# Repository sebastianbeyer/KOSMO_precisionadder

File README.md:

Precision adder based on [Doepfer A185-2](https://doepfer.de/a1852.htm) in KOSMO format.

You can use precision opamps, but I found that simple TL074 also work.
I could not get the 1V reference voltage to be exactly 1V, maybe my regulator was not great or my resitors were a bit off. 
I would suggest to use not 100 ohms for that, but maybe 500?

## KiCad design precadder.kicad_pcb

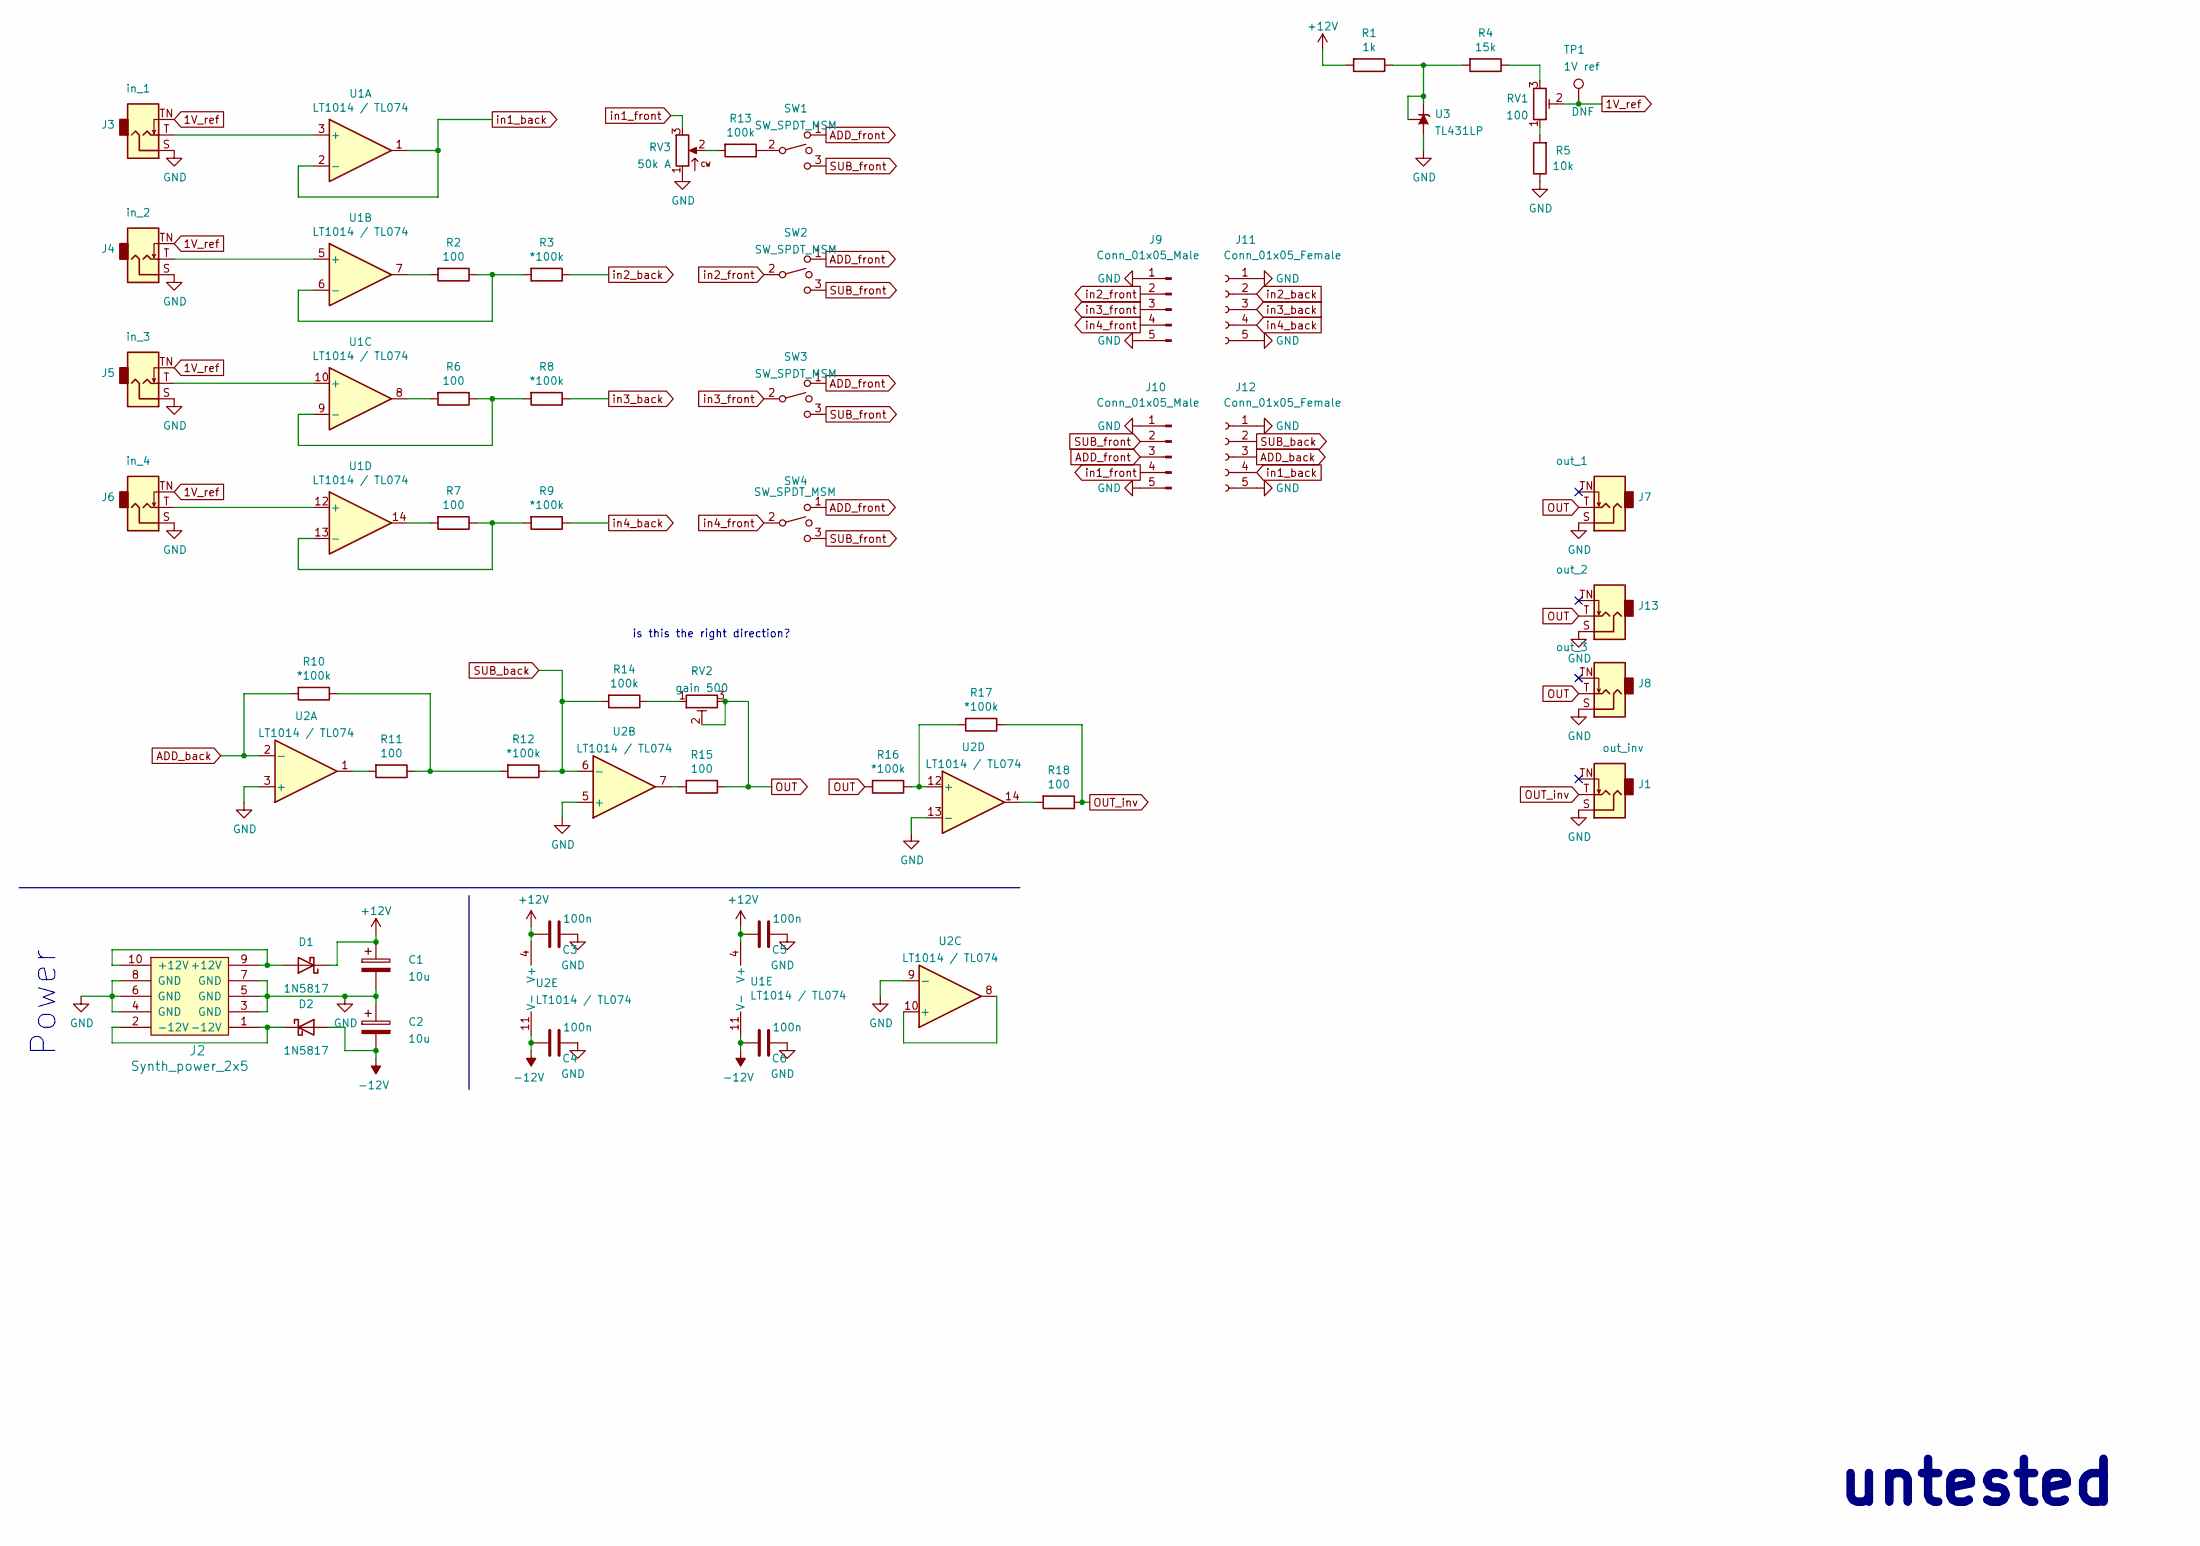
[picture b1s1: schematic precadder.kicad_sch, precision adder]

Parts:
C1, C2: 10u; CP_Radial_D6.3mm_P2.50mm
C3, C4, C5, C6: 100n; C_Disc_D3.0mm_W1.6mm_P2.50mm
D1, D2: 1N5817; D_DO-41_SOD81_P10.16mm_Horizontal
J1: out_inv; Jack_6.35mm_PJ_629HAN
J2: Synth_power_2x5; Power_Header
J3: in_1; Jack_6.35mm_PJ_629HAN
J4: in_2; Jack_6.35mm_PJ_629HAN
J5: in_3; Jack_6.35mm_PJ_629HAN
J6: in_4; Jack_6.35mm_PJ_629HAN
J7: out_1; Jack_6.35mm_PJ_629HAN
J8: out_3; Jack_6.35mm_PJ_629HAN
J9, J10: Conn_01x05_Male; PinHeader_1x05_P2.54mm_Vertical
J11, J12: Conn_01x05_Female; PinSocket_1x05_P2.54mm_Vertical
J13: out_2; Jack_6.35mm_PJ_629HAN
R1: 1k; R_Axial_DIN0207_L6.3mm_D2.5mm_P10.16mm_Horizontal
R2, R6, R7, R11, R15, R18: 100; R_Axial_DIN0207_L6.3mm_D2.5mm_P10.16mm_Horizontal
R3, R8, R9, R10, R12, R16, R17: *100k; R_Axial_DIN0207_L6.3mm_D2.5mm_P10.16mm_Horizontal
R4: 15k; R_Axial_DIN0207_L6.3mm_D2.5mm_P10.16mm_Horizontal
R5: 10k; R_Axial_DIN0207_L6.3mm_D2.5mm_P10.16mm_Horizontal
R13, R14: 100k; R_Axial_DIN0207_L6.3mm_D2.5mm_P10.16mm_Horizontal
RV1: 100; Potentiometer_Bourns_3296Z_Horizontal
RV2: gain 500; Potentiometer_Bourns_3296Z_Horizontal
RV3: 50k A; Potentiometer_Alpha_RD901F-40-00D_Single_Vertical_centered
SW1, SW2, SW3, SW4: SW_SPDT_MSM; SPDT-toggle-switch-1M-series
TP1: 1V ref; TestPoint_THTPad_D1.5mm_Drill0.7mm
U1, U2: LT1014 / TL074; DIP-14_W7.62mm_Socket_LongPads
U3: TL431LP; TO-92_Inline_Wide

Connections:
1V_ref: J3.TN, J4.TN, J5.TN, J6.TN, RV1.2, TP1.1
+12V: C1.1, C3.2, C5.2, D1.1 (K), R1.2, U1.4 (V+), U2.4 (V+)
-12V: C2.2, C4.2, C6.2, D2.2 (A), U1.11 (V-), U2.11 (V-)
ADD_back: J12.3, R10.2, U2.2 (-)
ADD_front: J10.3, SW1.1, SW2.1, SW3.1, SW4.1
GND: C1.2, C2.1, C3.1, C4.1, C5.1, C6.1, J1.S, J2.3 (GND), J2.4 (GND), J2.5 (GND), J2.6 (GND), J2.7 (GND), J2.8 (GND), J3.S, J4.S, J5.S, J6.S, J7.S, J8.S, J9.1, J9.5, J10.1, J10.5, J11.1, J11.5, J12.1, J12.5, J13.S, R5.1, RV3.1, U2.3 (+), U2.5 (+), U2.9 (-), U2.13 (-), U3.2 (A)
unnamed: D1.2 (A), J2.9 (+12V), J2.10 (+12V)
unnamed: D2.1 (K), J2.1 (-12V), J2.2 (-12V)
unnamed: J3.T, U1.3 (+)
unnamed: J4.T, U1.5 (+)
unnamed: J5.T, U1.10 (+)
unnamed: J6.T, U1.12 (+)
unnamed: R1.1, R4.2, U3.1 (REF), U3.3 (K)
unnamed: R2.1, R3.2, U1.6 (-)
unnamed: R2.2, U1.7
unnamed: R4.1, RV1.3
unnamed: R5.2, RV1.1
unnamed: R6.1, R8.2, U1.9 (-)
unnamed: R6.2, U1.8
unnamed: R7.1, R9.2, U1.13 (-)
unnamed: R7.2, U1.14
unnamed: R10.1, R11.1, R12.2
unnamed: R11.2, U2.1
unnamed: R13.1, SW1.2
unnamed: R13.2, RV3.2
unnamed: R14.1, RV2.1
unnamed: R15.2, U2.7
unnamed: R16.1, R17.2, U2.12 (+)
unnamed: R18.2, U2.14
unnamed: U2.8, U2.10 (+)
OUT: J7.T, J8.T, J13.T, R15.1, R16.2, RV2.2, RV2.3
OUT_inv: J1.T, R17.1, R18.1
SUB_back: J12.2, R12.1, R14.2, U2.6 (-)
SUB_front: J10.2, SW1.3, SW2.3, SW3.3, SW4.3
in1_back: J12.4, U1.1, U1.2 (-)
in1_front: J10.4, RV3.3
in2_back: J11.2, R3.1
in2_front: J9.2, SW2.2
in3_back: J11.3, R8.1
in3_front: J9.3, SW3.2
in4_back: J11.4, R9.1
in4_front: J9.4, SW4.2

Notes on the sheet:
untested
is this the right direction?
Power

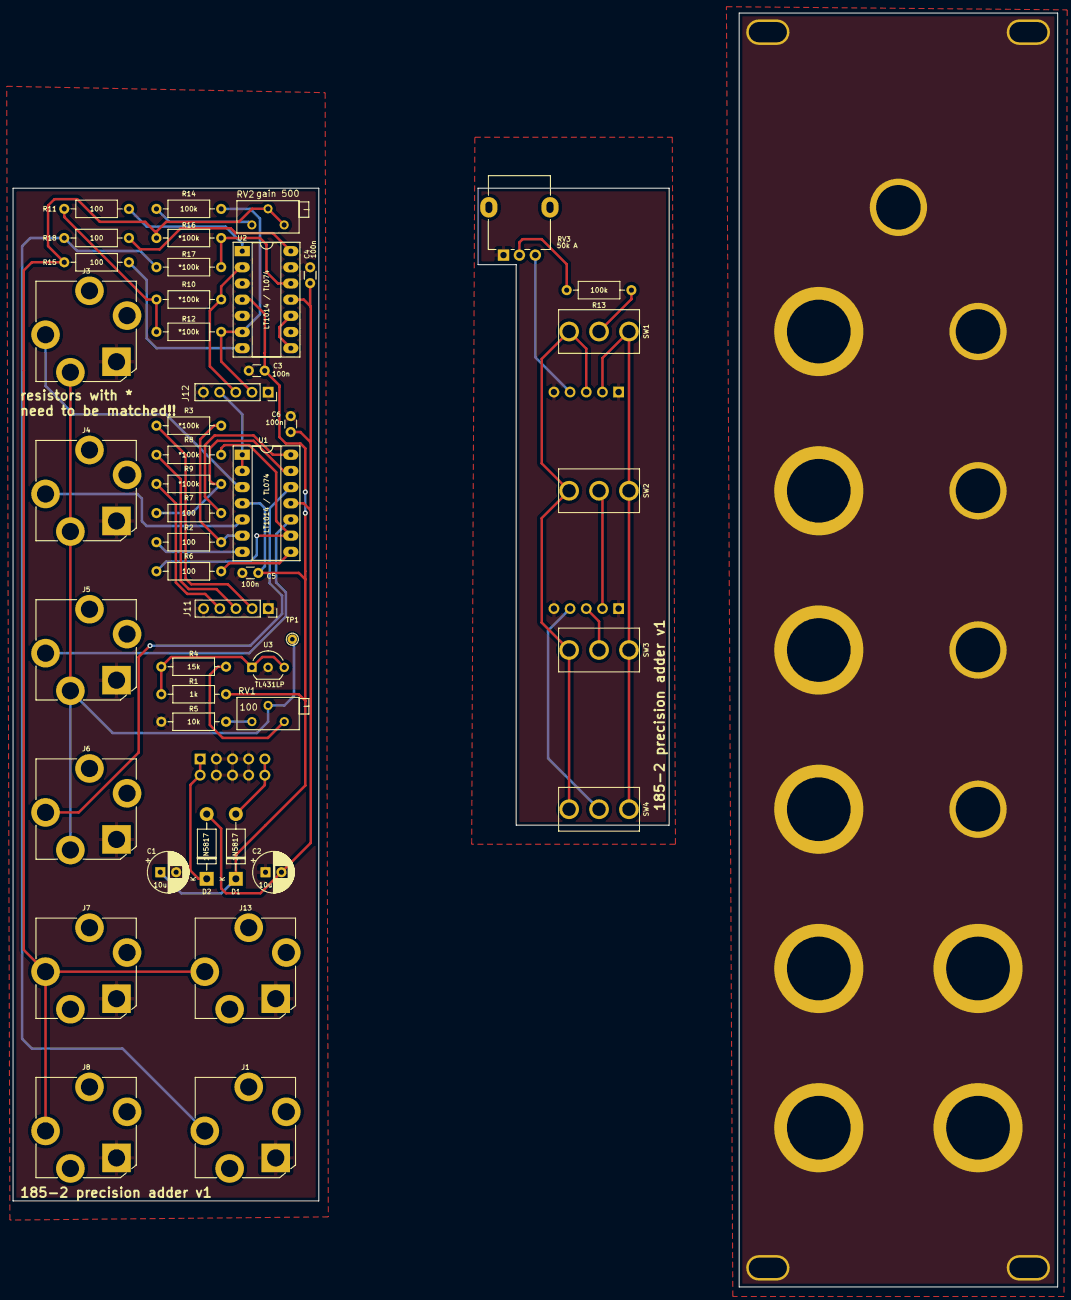
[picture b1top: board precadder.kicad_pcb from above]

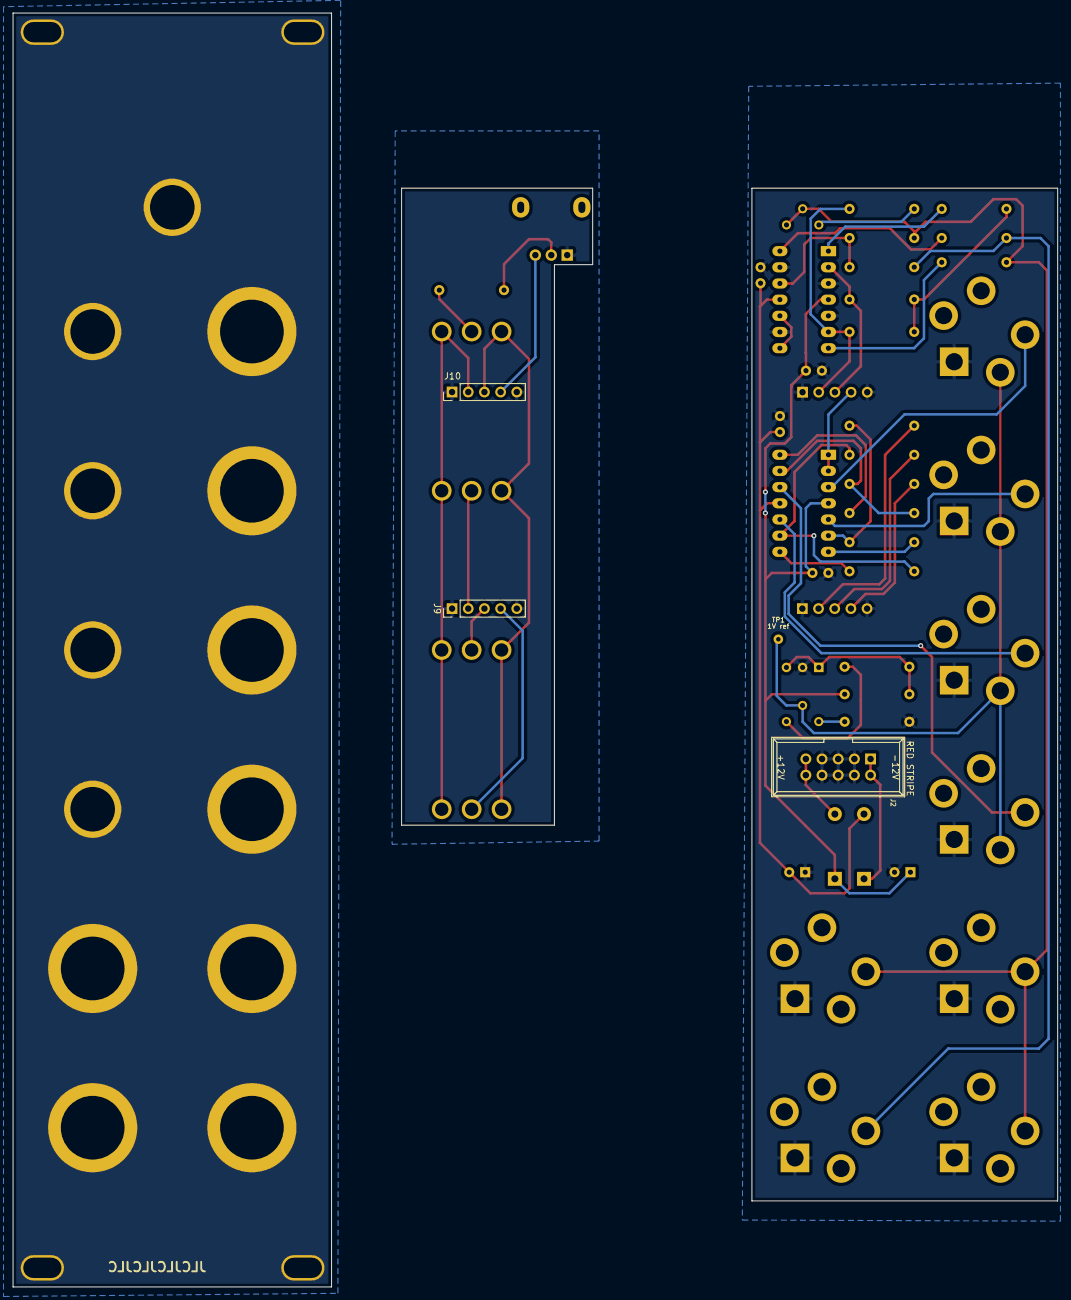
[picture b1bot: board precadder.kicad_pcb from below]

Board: 2 copper layers, 164.0 x 200.0 mm, 50 parts (3 on the bottom side), 42 nets.

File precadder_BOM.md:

# precadder.kicad_sch BOM

Tue 13 Dec 2022 10:33:28 CET

Generated from schematic by Eeschema 6.0.8-f2edbf62ab~116~ubuntu22.04.1

**Component Count:** 49

| Refs | Qty | Component | Description | Vendor | SKU |
| ----- | --- | ---- | ----------- | ---- | ---- |
| C1, C2 | 2 | 10u | Polarized capacitor | Tayda |  |
| C3, C4, C5, C6 | 4 | 100n | Unpolarized capacitor |  |  |
| D1, D2 | 2 | 1N5817 | Schottky Barrier Rectifier Diode, DO-41 | Tayda | A-159 |
| J1 | 1 | out_inv | Audio Jack, 2 Poles (Mono / TS), Switched T Pole (Normalling) | Tayda | A-1121 |
| J2 | 1 | Synth_power_2x5 | Pin header 2.54 mm 2x5 | Tayda | A-2939 |
| J3 | 1 | in_1 | Audio Jack, 2 Poles (Mono / TS), Switched T Pole (Normalling) | Tayda | A-1121 |
| J4 | 1 | in_2 | Audio Jack, 2 Poles (Mono / TS), Switched T Pole (Normalling) | Tayda | A-1121 |
| J5 | 1 | in_3 | Audio Jack, 2 Poles (Mono / TS), Switched T Pole (Normalling) | Tayda | A-1121 |
| J6 | 1 | in_4 | Audio Jack, 2 Poles (Mono / TS), Switched T Pole (Normalling) | Tayda | A-1121 |
| J7 | 1 | out_1 | Audio Jack, 2 Poles (Mono / TS), Switched T Pole (Normalling) | Tayda | A-1121 |
| J8 | 1 | out_3 | Audio Jack, 2 Poles (Mono / TS), Switched T Pole (Normalling) | Tayda | A-1121 |
| J9, J10 | 2 | Conn_01x05_Male | Generic connector, single row, 01x05, script generated (kicad-library-utils/schlib/autogen/connector/) |  |  |
| J11, J12 | 2 | Conn_01x05_Female | Generic connector, single row, 01x05, script generated (kicad-library-utils/schlib/autogen/connector/) |  |  |
| J13 | 1 | out_2 | Audio Jack, 2 Poles (Mono / TS), Switched T Pole (Normalling) | Tayda | A-1121 |
| R1 | 1 | 1k | Resistor | Tayda |  |
| R2, R6, R7, R11, R15, R18 | 6 | 100 | Resistor | Tayda |  |
| R3, R8, R9, R10, R12, R16, R17 | 7 | *100k | Resistor | Tayda |  |
| R4 | 1 | 15k | Resistor | Tayda |  |
| R5 | 1 | 10k | Resistor | Tayda |  |
| R13, R14 | 2 | 100k | Resistor | Tayda |  |
| RV1 | 1 | 100 | Trim-potentiometer | https://www.reichelt.de/praezisionspotentiometer-25-gaenge-s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 | maybe not 100ohm, but more like 500? |
| RV2 | 1 | gain 500 | Trim-potentiometer | Tayda |  |
| RV3 | 1 | 50k A | Potentiometer | Tayda |  |
| SW1, SW2, SW3, SW4 | 4 | SW_SPDT_MSM | Switch, single pole double throw, center OFF position | Tayda | A-3187 |
| U1, U2 | 2 | LT1014 / TL074 | Quad operational amplifier, DIP-14 | Tayda | A-1138 |
| U3 | 1 | TL431LP | Shunt Regulator, TO-92 |  |  |

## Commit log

2022-12-13 initial
2022-12-13 add panel art
2022-12-13 add readme
2022-12-13 add pdf of schematic
